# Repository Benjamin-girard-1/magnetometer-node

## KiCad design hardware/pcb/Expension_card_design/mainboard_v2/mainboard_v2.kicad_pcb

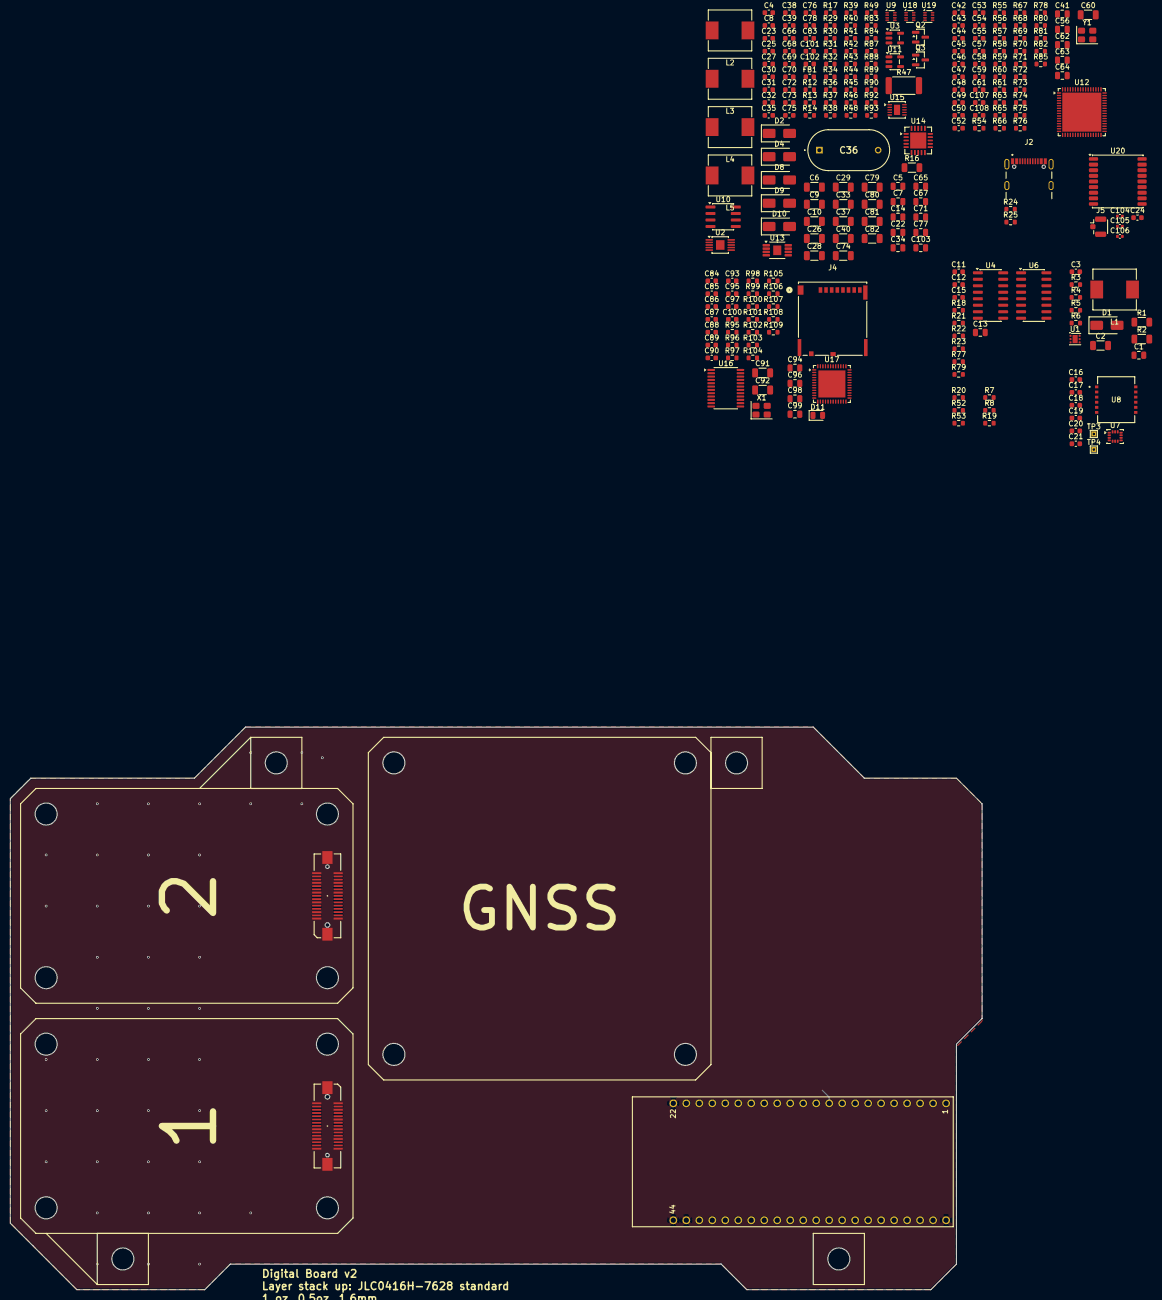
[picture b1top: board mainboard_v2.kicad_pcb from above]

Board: 4 copper layers, 190.0 x 110.0 mm, 260 parts (0 on the bottom side), 178 nets.

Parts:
C1, C7, C13, C22, C34, C41, C56, C65, C67, C71, C77, C96: 10u; C_0805_2012Metric
C2, C6, C9, C10, C37, C40, C79, C80, C81, C82, C91, C92: 4u7; C_1206_3216Metric
C3, C66, C68, C73, C78: 10n; C_0603_1608Metric
C4: 22p; C_0603_1608Metric
C5, C14, C62, C63, C64, C94, C98, C99, C103: 1u; C_0805_2012Metric
C8, C11, C12, C15, C16, C17, C18, C19, C20, C21, C23, C25, C38, C39, C42, C43, C44, C45, C46, C47, C48, C55, C58, C59, C61, C69, C72, C76, C84, C85, C86, C87, C88, C89, C90, C93, C95, C101, C102: 100n; C_0603_1608Metric
C24: 10u; C_0603_1608Metric
C26, C28: 22u; C_1206_3216Metric
C27, C97, C100: 15p; C_0603_1608Metric
C29, C33, C60, C74: 47u; C_1206_3216Metric
C30, C83: 4n7; C_0603_1608Metric
C31, C75: 10p; C_0603_1608Metric
C32, C35: 22n; C_0603_1608Metric
C36: 470mF; C_Radial_D8.0mm_P11.50mm
C49, C50, C52, C53, C54, C57, C107, C108: 1n; C_0603_1608Metric
C70: 220n; C_0603_1608Metric
C104, C105, C106: 100n; C_0402_1005Metric
D1, D2, D4, D8, D9, D10: SS34; D_SMA
D11: LED; LED_0805_2012Metric
FB1: 120Ω@100MHz 2A 50mΩ; L_0603_1608Metric
H1, H2, H3, H4, H5, H6, H7, H8, H9, H10, H11, H12, H13, H14, H15, H16: MountingHole; MountingHole_4.3mm_M4
J1, J3: 550910374; CONN_MOLEX_02x15_55091-0374
J2: USB_C_Receptacle_USB2.0_16P; GCT_USB4105-GF-A
J4: Micro_SD_CARD; CONN_503398-1892_MOL
J5: Conn_Coaxial; U.FL_Hirose_U.FL-R-SMT-1_Vertical
L1, L2, L3, L4, L5: 10u; ZEMS0850-100M_8.5x8.0mm
Q2: AO3401A; SOT-23
Q3: AO3400A; SOT-23
R1, R2: 0; R_1206_3216Metric
R3: 49k9; R_0603_1608Metric
R4, R7, R8, R17, R29, R31, R41, R42, R49, R52, R53, R56, R70, R73, R75, R78, R87, R90, R93, R95, R96, R108: 100k; R_0603_1608Metric
R5, R18, R19, R20, R39, R58, R77, R79, R97, R99, R100, R101, R102, R103, R104, R107, R109: 10k; R_0603_1608Metric
R6: 3k6; R_0603_1608Metric
R12, R92: 510k; R_0603_1608Metric
R13, R55, R80, R105: 1k; R_0603_1608Metric
R14, R48: 200k; R_0603_1608Metric
R16: 90k9; R_1206_3216Metric
R21, R22, R23, R57, R59, R60, R61, R63, R65, R66, R67, R68, R69, R71, R72, R74, R76, R81, R82, R85: 22; R_0603_1608Metric
R24, R25: 5k1; R_0603_1608Metric
R30, R32, R34, R37, R54: 300k; R_0603_1608Metric
R36: R_0603_1608Metric
R38, R43: 75k; R_0603_1608Metric
R40: 24k; R_0603_1608Metric
R44, R83: 39k; R_0603_1608Metric
R45, R46: 100; R_0603_1608Metric
R47: 22; R_2512_6332Metric
R84, R98: 12k; R_0603_1608Metric
R88: 330k; R_0603_1608Metric
R89: 10; R_0603_1608Metric
R106: 68k; R_0603_1608Metric
TP3, TP4: TestPoint; TestPoint_THTPad_1.0x1.0mm_Drill0.5mm
U1: TPS61170; WSON-6-1EP_2x2mm_P0.65mm_EP1x1.6mm
U2: LT3042xMSE; MSOP-10-1EP_3x3mm_P0.5mm_EP1.68x1.88mm
U3: TPS61040DBV; SOT-23-5
U4, U6: 74HC595D,118; SOIC-16_3.9x9.9mm_P1.27mm
U5: ESP32-S3-DevKitC; MODULE_ESP32-S3-DEVKITC
U7: LSM6DSVETR; LGA-14_3x2.5mm_P0.5mm_LayoutBorder3x4y
U8: SCL3300-D01-10; SCL3300-D01-10_MUR
U9, U18: TPS2116DRL; SOT-583-8
U10: TPS54331DR; SOIC-8_3.9x4.9mm_P1.27mm
U11: TPS7A2033PDBVR; SOT-23-5
U12: AD7779ACPZ; QFN-64-1EP_9x9mm_P0.5mm_EP7.65x7.65mm
U13: TPS7A4901DGNR; HVSSOP-8-1EP_3x3mm_P0.65mm_EP1.57x1.89mm
U14: TPS7A3301RGWR; Texas_RGW0020A_VQFN-20-1EP_5x5mm_P0.65mm_EP3.15x3.15mm
U15: TPS63700DRCR; VSON-10-1EP_3x3mm_P0.5mm_EP1.2x2mm
U16: TS3A27518EPWR; TSSOP-24_4.4x7.8mm_P0.65mm
U17: USB2641-HZH-02; QFN-48-1EP_7x7mm_P0.5mm_EP5.3x5.3mm
U19: TPS62933; SOT-583-8
U20: MAX-M10S; ublox_MAX
X1: X322524MOB4SI; Crystal_SMD_3225-4Pin_3.2x2.5mm
Y1: OT2JI-111-8.192M; Crystal_SMD_3225-4Pin_3.2x2.5mm

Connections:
+1V65: J1.17, J3.17, U12.57 (VCM)
+3V3: C11.1, C12.1, C13.1, C15.1, C16.2, C17.2, C18.2, C19.2, C24.1, C29.1, C47.1, C55.1, C56.1, C84.1, C85.1, C86.1, C87.1, C88.1, C89.1, C90.1, C91.1, C92.1, C93.1, C94.2, C95.1, C96.1, C104.1, C105.1, C106.1, J4.4 (VDD), L3.2, R18.1, R19.2, R20.2, R29.1, R38.1, R42.1, R58.2, R75.1, R77.1, R78.1, R79.1, R95.1, R96.1, R97.1, R99.1, R100.1, R101.1, R102.1, R103.1, R104.1, U4.16 (VCC), U5.1 (ESP_3V3), U5.2 (ESP_3V3), U6.16 (VCC), U7.5 (VDD_IO), U7.8 (VDD), U8.4 (VDD), U8.9 (DVIO), U12.24 (IOVDD), U16.8 (VCC), U17.5 (VDD33), U17.12 (VDD33), U17.16 (VDD33), U17.25 (VDD33), U17.34 (VDD33), U17.41 (VDD33), U17.48 (VDD33), U20.6 (V_BCKP), U20.7 (VCC_IO), U20.8 (VCC), Y1.4 (VDD)
+3V3A: C39.1, C40.1, C41.1, C42.1, C43.1, C44.1, C45.1, C46.1, J1.22, J3.22, U11.5 (OUT), U12.6 (AVDD1A), U12.43 (AVDD1B), U12.52 (AVDD2B), U12.54 (FORMAT1), U12.55 (FORMAT0), U12.58 (AVDD2A), U12.62 (AVDD4)
+3V3D: J1.23, J3.23
+5V: C10.1, C23.2, C37.1, C38.1, C77.1, C103.1, L2.1, Q2.2, R1.1, R30.2, R44.1, R89.2, U3.5 (VIN), U9.3 (VIN1), U9.5 (MODE), U11.1 (IN), U15.5 (IN), U18.2 (VOUT), U18.7 (VOUT)
+5VA: C66.1, C67.1, J1.19, J3.19, R83.1, U13.1 (OUT)
+9VA: C6.1, J1.21, J3.21, R54.1, U2.9 (OUTS), U2.10 (OUT)
+10V: C4.1, C5.1, C7.1, C8.1, C65.1, D2.1 (K), R12.1, U2.1 (IN), U2.2 (IN), U2.3 (EN/UV), U2.6 (PGFB), U13.5 (EN), U13.8 (IN)
+18V: J1.18, J3.18, R2.2
-5VA: C73.1, C74.1, J1.20, J3.20, R88.1, U14.1 (OUT), U14.20 (OUT)
-6V2: C71.1, C72.1, C78.1, C79.1, C80.1, C81.1, C82.1, D10.2 (A), R92.2, R93.2, U14.13 (EN), U14.15 (IN), U14.16 (IN), U15.8 (OUT)
/ADC_AD777x/ADC_9VA_MON: C48.1, R54.2, R55.1, R56.1
/ADC_AD777x/ADC_9VA_MON_FLT: R55.2, U12.63 (AUXAIN+)
/ADC_AD777x/ADC_AREG1CAP: C63.1, U12.59 (AREG1CAP)
/ADC_AD777x/ADC_AREG2CAP: C64.1, U12.51 (AREG2CAP)
/ADC_AD777x/ADC_CONVST_SAR: R70.1, U6.5 (QF), U12.17 (CONVST_SAR)
/ADC_AD777x/ADC_CS: R21.1, R58.1, U12.18 (ALERT/~CS)
/ADC_AD777x/ADC_DRDY: U5.16 (GPIO10), U12.30 (~DRDY)
/ADC_AD777x/ADC_DREGCAP: C62.1, U12.23 (DREGCAP)
/ADC_AD777x/ADC_IN0+: C49.1, R57.2, U12.2 (AIN0+)
/ADC_AD777x/ADC_IN0-: C49.2, R59.2, U12.1 (AIN0-)
/ADC_AD777x/ADC_IN1+: C50.1, R60.2, U12.4 (AIN1+)
/ADC_AD777x/ADC_IN1-: C50.2, R63.2, U12.3 (AIN1-)
/ADC_AD777x/ADC_IN2+: C52.1, R65.2, U12.10 (AIN2+)
/ADC_AD777x/ADC_IN2-: C52.2, R67.2, U12.9 (AIN2-)
/ADC_AD777x/ADC_IN3+: C57.1, C107.1, R66.2, R74.2, U12.12 (AIN3+), U12.37 (AIN7+)
/ADC_AD777x/ADC_IN3-: C57.2, C107.2, R76.2, R81.2, U12.11 (AIN3-), U12.38 (AIN7-)
/ADC_AD777x/ADC_IN4+: C53.1, R68.2, U12.47 (AIN4+)
/ADC_AD777x/ADC_IN4-: C53.2, R69.2, U12.48 (AIN4-)
/ADC_AD777x/ADC_IN5+: C54.1, R71.2, U12.45 (AIN5+)
/ADC_AD777x/ADC_IN5-: C54.2, R72.2, U12.46 (AIN5-)
/ADC_AD777x/ADC_IN6+: C108.1, R82.2, U12.39 (AIN6+)
/ADC_AD777x/ADC_IN6-: C108.2, R85.2, U12.40 (AIN6-)
/ADC_AD777x/ADC_MCLK: U12.32 (XTAL2/MCLK), Y1.3 (OUT)
/ADC_AD777x/ADC_MCLK_EN: R78.2, U6.4 (QE), Y1.1 (Tri-State)
/ADC_AD777x/ADC_REF+: C58.1, C59.1, C60.1, R80.1, U12.8 (REF1+), U12.41 (REF2+)
/ADC_AD777x/ADC_REF_OUT: C61.1, R80.2, U12.49 (REF_OUT)
/ADC_AD777x/ADC_RESET: R75.2, U6.2 (QC), U12.36 (~RESET)
/ADC_AD777x/ADC_SCLK: R22.1, U12.19 (DCLK2/SCLK)
/ADC_AD777x/ADC_SDI: R23.1, U12.20 (DCLK1/SDI)
/ADC_AD777x/ADC_SDO: R61.2, U5.20 (GPIO14)
/ADC_AD777x/ADC_SDO_R: R61.1, U12.21 (DCLK0/SDO)
/ADC_AD777x/ADC_START: R73.1, U6.3 (QD), U12.33 (~START)
/ADC_AD777x/AIN0+: J3.4, R59.1
/ADC_AD777x/AIN0-: J3.5, R57.1
/ADC_AD777x/AIN1+: J3.11, R63.1
/ADC_AD777x/AIN1-: J3.10, R60.1
/ADC_AD777x/AIN2+: J3.8, R65.1
/ADC_AD777x/AIN2-: J3.7, R67.1
/ADC_AD777x/AIN4+: J1.11, R69.1
/ADC_AD777x/AIN4-: J1.10, R68.1
/ADC_AD777x/AIN5+: J1.7, R71.1
/ADC_AD777x/AIN5-: J1.8, R72.1
/ADC_AD777x/AIN7+: J1.5, R74.1
/ADC_AD777x/AIN7-: J1.4, R76.1
/ADC_AD777x/TH1+: J3.13, R66.1
/ADC_AD777x/TH1-: J3.14, R81.1
/ADC_AD777x/TH2+: J1.13, R82.1
/ADC_AD777x/TH2-: J1.14, R85.1
/DATA_SAVING/+5VBUS: J2.A4 (VBUS), J2.B4 (VBUS), R106.1, R108.1
/DATA_SAVING/CC1: J2.B5 (CC2), R25.1
/DATA_SAVING/CC2: J2.A5 (CC1), R24.1
/DATA_SAVING/CRFLIT: C99.1, U17.15 (CRFILT)
/DATA_SAVING/D+: J2.A6 (D+), J2.B6 (D+), U17.42 (USB+)
/DATA_SAVING/D-: J2.A7 (D-), J2.B7 (D-), U17.43 (USB-)
/DATA_SAVING/EN_SD_MUX: R96.2, U4.6 (QG), U16.20 (~EN)
/DATA_SAVING/E_CLK: R101.2, U5.5 (GPIO5), U16.23 (NC3)
/DATA_SAVING/E_CMD: R102.2, U5.9 (GPIO16), U16.21 (NC4)
/DATA_SAVING/E_D0: R100.2, U5.6 (GPIO5), U16.1 (NC2)
/DATA_SAVING/E_D1: R99.2, U5.4 (GPIO4), U16.2 (NC1)
/DATA_SAVING/E_D2: R104.2, U5.7 (GPIO7), U16.22 (NC6)
/DATA_SAVING/E_D3: R103.2, U5.8 (GPIO15), U16.19 (NC5)
/DATA_SAVING/LED_IN: D11.2 (A), R105.2
/DATA_SAVING/LED_OUT: R105.1, U17.37 (LED)
/DATA_SAVING/MCLK: J4.5 (CLK), U16.7 (COM3)
/DATA_SAVING/MCMD: J4.3 (CMD), U16.9 (COM4)
/DATA_SAVING/MD0: J4.7 (DAT0), U16.6 (COM2)
/DATA_SAVING/MD1: J4.8 (DAT1), U16.4 (COM1)
/DATA_SAVING/MD2: J4.1 (DAT2), U16.12 (COM6)
/DATA_SAVING/MD3: J4.2 (DAT3), U16.10 (COM5)
/DATA_SAVING/PLL_FLIT: C98.1, U17.46 (PLLFILT)
/DATA_SAVING/RBIAS: R98.1, U17.47 (RBIAS)
/DATA_SAVING/SD_MUX_SEL: R95.2, U4.15 (QA), U16.14 (IN2), U16.24 (IN1)
/DATA_SAVING/SD_WP: R109.1, U17.13 (SD_WP)
/DATA_SAVING/SD_nCD: R107.1, U17.14 (SD_nCD)
/DATA_SAVING/USB2641_XTAL1: C100.1, U17.45 (XTAL1), X1.1
/DATA_SAVING/USB2641_XTAL2: C97.1, U17.44 (XTAL2), X1.3
/DATA_SAVING/USB2641_nRESET: R97.2, U4.5 (QF), U17.38 (nRESET)
/DATA_SAVING/USB_CLK: U16.15 (NO3), U17.21 (SD_CLK)
/DATA_SAVING/USB_CMD: U16.17 (NO4), U17.24 (SD_CMD)
/DATA_SAVING/USB_D0: U16.13 (NO2), U17.18 (SD_D0)
/DATA_SAVING/USB_D1: U16.11 (NO1), U17.17 (SD_D1)
/DATA_SAVING/USB_D2: U16.16 (NO6), U17.33 (SD_D2)
/DATA_SAVING/USB_D3: U16.18 (NO5), U17.32 (SD_D3)
/DATA_SAVING/VBUS_DET_3V: R106.2, U17.39 (VBUS_DET)
/DEVICE_DETECT_1: J3.2, R20.1, U5.13 (GPIO3)
/DEVICE_DETECT_2: J1.2, R19.1, U5.12 (GPIO8)
/GNSS/GPS_RX: U5.38 (GPIO48), U20.2 (TXD)
/GNSS/GPS_TX: U5.37 (GPIO45), U20.3 (RXD)
/IMU/CS_SCL: U5.14 (GPIO46), U8.5 (CS)
/IMU/MISO: U5.15 (GPIO9), U7.1 (SDO), U8.6 (MISO)
/IMU/MOSI: U5.11 (GPIO18), U7.14 (SDA), U8.7 (MOSI)
/IMU/SCLK: U5.10 (GPIO17), U7.13 (SCL), U8.8 (SCK)
/MCU_ESP32S3/EN_BST_18V: R4.1, U1.5 (CTRL), U4.3 (QD)
/MCU_ESP32S3/EN_SUPERCAP_CHARGE: R46.2, U5.28 (GPIO42)
/MCU_ESP32S3/ESP_CS: R21.2, U5.17 (GPIO11)
/MCU_ESP32S3/ESP_SCLK: R22.2, U5.18 (GPIO12)
/MCU_ESP32S3/ESP_SDO: R23.2, U5.19 (GPIO13)
/MCU_ESP32S3/SR_CHAIN_DATA: U4.9 (QH'), U6.14 (SER)
/MCU_ESP32S3/SR_DATA: U4.14 (SER), U5.42 (GPIO19)
/MCU_ESP32S3/SR_LATCH: U4.12 (RCLK), U5.40 (GPIO21), U6.12 (RCLK)
/MCU_ESP32S3/SR_OE_N: R18.2, U4.13 (~OE), U5.41 (GPIO20), U6.13 (~OE)
/MCU_ESP32S3/SR_SHIFT_CLK: U4.11 (SRCLK), U5.39 (GPIO47), U6.11 (SRCLK)
/POWER/5V_HOLDUP_CAP: C14.1, D9.1 (K), U9.6 (VIN2)
/POWER/5V_STEP_DOWN_IN: C28.1, R48.1, U9.2 (VOUT), U9.7 (VOUT), U10.2 (VIN)
/POWER/5V_SUPERCAP: C36.1, D9.2 (A), R47.2
/POWER/5V_USB_PRESENT: R29.2, U9.8 (ST)
/POWER/+5V_SOLAR: C27.2, C33.1, C102.2, L5.2, R32.2, R37.2, U18.3 (VIN1), U18.5 (MODE)
/POWER/BST_10V_FB: C4.2, R14.2, R17.1, U3.3 (FB)
/POWER/BST_10V_FB_DIV: R12.2, R14.1
/POWER/BST_10V_SW: D2.2 (A), L2.2, U3.1 (SW)
/POWER/INV_N5V5_COMP: C83.1, U15.1 (COMP)
/POWER/INV_N5V5_FB: C75.1, R87.2, R92.1, U15.9 (FB)
/POWER/INV_N5V5_FF: C75.2, R93.1
/POWER/INV_N5V5_SW: D10.1 (K), L4.1, U15.6 (SW)
/POWER/INV_N5V5_VIN: C69.1, R89.1, U15.3 (VIN)
/POWER/INV_N5V5_VREF: C70.1, R87.1, U15.10 (VREF)
/POWER/LDO_9V_ILIM: R13.2, U2.5 (ILIM)
/POWER/LDO_9V_SET: C9.1, R16.1, U2.7 (SET)
/POWER/LDO_N5V_FB: C73.2, R88.2, R90.1, U14.3 (FB)
/POWER/LDO_N5V_NR: C76.1, U14.14 (NR/SS)
/POWER/LDO_P5V_FB: C66.2, R83.2, R84.1, U13.2 (FB)
/POWER/LDO_P5V_NR: C68.1, U13.6 (NR/SS)
/POWER/SOLAR_PRESENT: R42.2, U18.8 (ST)
/POWER/SOLAR_VOLTAGE: C34.1, C101.2, R34.2, U19.3 (VIN)
/POWER/STPD_3V3_BOOT: C26.1, U10.1 (BOOT)
/POWER/STPD_3V3_COMP: C30.1, C31.1, U10.6 (COMP)
/POWER/STPD_3V3_COMP_F: C30.2, R39.1
/POWER/STPD_3V3_PH: C26.2, D4.1 (K), L3.1, U10.8 (PH)
/POWER/STPD_3V3_SS: C32.1, U10.4 (SS)
/POWER/STPD_3V3_VSENS: R38.2, R40.1, U10.5 (VSENSE)
/RESET_1: J3.26, R52.1, U6.6 (QG)
/RESET_2: J1.26, R7.1, U6.15 (QA)
/SCL_1: J3.28, U5.30 (GPIO40)
/SCL_2: J1.28, U5.27 (GPIO2)
/SDA_1: J3.29, U5.29 (GPIO41)
/SDA_2: J1.29, U5.26 (GPIO1)
/SENSOR_SET_RESET_DRIVER/+18V_OUT: C2.1, D1.1 (K), R2.1, R3.1
/SENSOR_SET_RESET_DRIVER/BST_18V_COMP: R5.1, U1.2 (COMP)
/SENSOR_SET_RESET_DRIVER/BST_18V_COMP_FILT: C3.1, R5.2
/SENSOR_SET_RESET_DRIVER/BST_18V_FB: R3.2, R6.1, U1.1 (FB)
/SENSOR_SET_RESET_DRIVER/BST_18V_IN: C1.1, L1.1, R1.2, U1.6 (VIN)
/SENSOR_SET_RESET_DRIVER/BST_18V_SW: D1.2 (A), L1.2, U1.4 (SW)
/SET_1: J3.25, R53.1, U6.7 (QH)
/SET_2: J1.25, R8.1, U6.1 (QB)
GND: C1.2, C2.2, C3.2, C5.2, C6.2, C7.2, C8.2, C9.2, C10.2, C11.2, C12.2, C13.2, C14.2, C15.2, C16.1, C17.1, C18.1, C19.1, C20.1, C21.1, C22.2, C23.1, C24.2, C28.2, C29.2, C31.2, C32.2, C33.2, C34.2, C35.2, C36.2, C37.2, C38.2, C39.2, C40.2, C41.2, C42.2, C43.2, C44.2, C45.2, C46.2, C47.2, C48.2, C55.2, C56.2, C58.2, C59.2, C60.2, C61.2, C62.2, C63.2, C64.2, C65.2, C67.2, C68.2, C69.2, C70.2, C71.2, C72.2, C74.2, C76.2, C77.2, C78.2, C79.2, C80.2, C81.2, C82.2, C83.2, C84.2, C85.2, C86.2, C87.2, C88.2, C89.2, C90.2, C91.2, C92.2, C93.2, C94.1, C95.2, C96.2, C97.2, C98.2, C99.2, C100.2, C101.1, C102.1, C103.2, C104.2, C105.2, C106.2, D4.2 (A), D11.1 (K), J1.1, J1.3, J1.6, J1.9, J1.12, J1.15, J1.16, J1.24, J1.27, J1.30, J1.P1, J1.P2, J2.A1 (GND), J2.B1 (GND), J2.S1 (SHIELD), J3.1, J3.3, J3.6, J3.9, J3.12, J3.15, J3.16, J3.24, J3.27, J3.30, J3.P1, J3.P2, J4.6 (VSS), J4.10 (SHIELD), J4.11 (VSS), J4.12 (VSS), J4.13 (VSS), J4.14 (VSS), J5.2 (Ext_2), L4.2, Q3.2, R4.2, R6.2, R7.2, R8.2, R13.1, R16.2, R17.2, R24.2, R25.2, R31.2, R36.2, R39.2, R40.2, R41.2, R43.2, R49.2, R52.2, R53.2, R56.2, R70.2, R73.2, R84.2, R90.2, R98.2, R107.2, R108.2, R109.2, U1.3 (GND), U1.7 (TP), U2.8 (GND), U2.11 (GND), U3.2 (GND), U4.8 (GND), U5.22 (GND), U5.23 (GND), U5.43 (GND), U5.44 (GND), U6.8 (GND), U7.2 (SDx), U7.3 (SCx), U7.6 (GND), U7.7 (GND), U8.1 (AVSS), U8.3 (RESERVED), U8.11 (DVSS), U8.12 (EMC_GND), U9.1 (GND), U10.7 (GND), U11.2 (GND), U11.4 (NC), U12.5 (AVSS1A), U12.7 (REF1-), U12.22 (DGND), U12.31 (XTAL1), U12.42 (REF2-), U12.44 (AVSS1B), U12.50 (AVSS2B), U12.53 (AVSS3), U12.56 (CLK_SEL), U12.60 (AVSS2A), U12.61 (AVSS4), U12.64 (AUXAIN-), U12.65 (EPAD(AVSSx)), U13.3 (NC), U13.4 (GND), U13.9 (PwPd), U14.7 (GND), U14.21 (EP), U15.2 (GND), U15.7 (PSGND), U15.11 (PowerPAD), U16.5 (GND), U17.40 (TEST), U17.49 (GND), U18.1 (GND), U19.4 (GND), U20.1 (GND), U20.10 (GND), U20.12 (GND), X1.2, X1.4, Y1.2 (GND)
unnamed: D8.2 (A), Q2.3
unnamed: D8.1 (K), R47.1
unnamed: Q2.1, R45.2
unnamed: Q3.1, R46.1, R49.1
unnamed: Q3.3, R44.2, R45.1
unnamed: R77.2, U4.10 (~SRCLR)
unnamed: R79.2, U6.10 (~SRCLR)
unnamed: TP3.1 (1_1), U7.4 (INT1)
unnamed: TP4.1 (1_1), U7.9 (INT2)
unnamed: C21.2, U8.2 (A_EXTC)
unnamed: C20.2, U8.10 (D_EXTC)
unnamed: R30.1, R31.1, U9.4 (PR1)
unnamed: R43.1, R48.2, U10.3 (EN)
unnamed: U12.34 (~SYNC_OUT), U12.35 (~SYNC_IN)
unnamed: R37.1, R41.1, U18.4 (PR1)
unnamed: C22.1, FB1.2, U18.6 (VIN2)
unnamed: C25.2, U19.6 (BST)
unnamed: R34.1, U19.2 (EN)
unnamed: C27.1, R32.1, U19.8 (FB)
unnamed: R36.1, U19.1 (RT)
unnamed: C35.1, U19.7 (SS)
unnamed: C25.1, L5.1, U19.5 (SW)

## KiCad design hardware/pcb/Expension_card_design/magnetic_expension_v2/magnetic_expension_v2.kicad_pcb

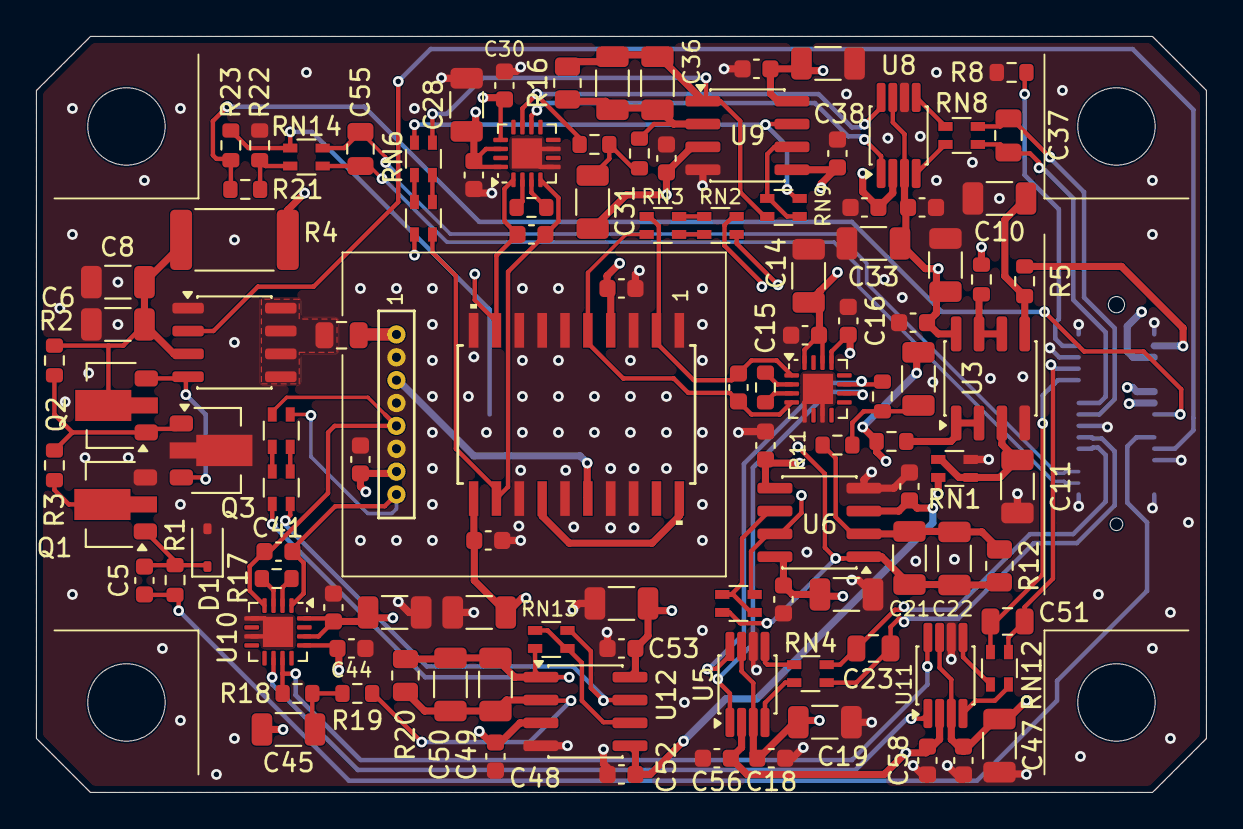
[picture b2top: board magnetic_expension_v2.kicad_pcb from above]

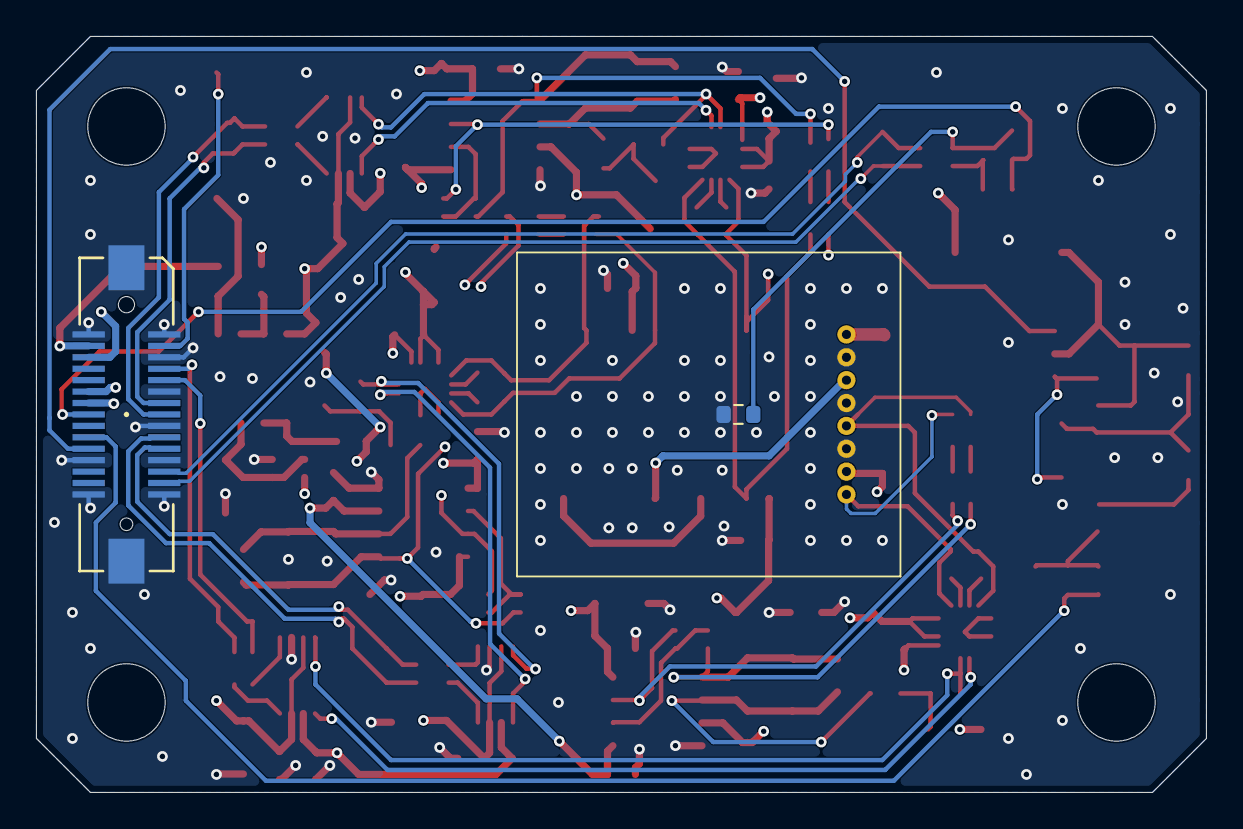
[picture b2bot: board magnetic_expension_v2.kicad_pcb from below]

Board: 4 copper layers, 65.0 x 42.0 mm, 118 parts (2 on the bottom side), 79 nets.

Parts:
C1, C6, C8: 10u; C_1206_3216Metric
C2, C3, C4, C9, C15, C16, C18, C20, C24, C25, C29, C30, C32, C34, C38, C39, C43, C44, C46, C48, C52, C53, C56, C57, C58: 100n; C_0603_1608Metric
C5: 1n; C_0603_1608Metric
C7, C23, C37, C51, C55: 220n; C_0805_2012Metric
C10, C11, C12, C14, C19, C21, C22, C26, C28, C33, C35, C36, C40, C42, C47, C49, C50, C54: 4u7; C_1206_3216Metric
C13, C27, C41: 10n; C_0603_1608Metric
C17, C31, C45: 47u; C_1206_3216Metric
D1: 1N4148WS; D_SOD-323
H1, H2, H3, H4: MountingHole; MountingHole_4.3mm_M4
J1: 528850374; CONN_MOLEX_02x15_52885-0374
Q1, Q2: D882; SOT-89-3
Q3: B772; SOT-89-3
Q4: DMC3028LSD; SO-8_3.9x4.9mm_P1.27mm
R1, R2, R3, R5: 1k; R_0603_1608Metric
R4: 220; R_2512_6332Metric
R6, R7: 20; R_0603_1608Metric
R8, R11, R15, R19: 20k; R_0603_1608Metric
R9, R13, R17: 120; R_0603_1608Metric
R10, R14, R18: 300k; R_0603_1608Metric
R12, R16, R20: 100M; R_0805_2012Metric
R21, R22, R23: 100k; R_0603_1608Metric
RN1: 10k; R_Array_Convex_2x0603
RN2, RN3, RN5, RN6, RN7, RN9, RN10, RN11, RN13: 20k; R_Array_Convex_2x0603
RN4, RN8, RN12, RN14: 1k; R_Array_Convex_2x0603
TH1: 100k NTC; R_0603_1608Metric
U1: HMC1001-RC; SIP8_HMC1001_HNW
U2: HMC1002-TR; SOIC20_HNW
U3, U6, U9, U12: OPA2197xD; SOIC-8_3.9x4.9mm_P1.27mm
U4, U7, U10: INA851RGTR; VQFN-16-1EP_3x3mm_P0.5mm_EP1.68x1.68mm
U5, U8, U11: THP210DGK; VSSOP-8_3x3mm_P0.65mm

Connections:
+1V65: J1.17, R5.1
+1V65B: C56.1, C57.1, C58.1, R7.2, U5.2 (VCM), U8.2 (VCM), U11.2 (VCM)
+3V3A: J1.23, R21.2, R23.2
+4V5B: C16.1, C17.2, C20.1, C24.1, C30.1, C31.2, C34.1, C38.1, C44.1, C45.2, C48.1, C52.1, R6.2, U4.13 (VOCM), U6.3 (+), U6.5 (+), U7.13 (VOCM), U9.3 (+), U9.5 (+), U10.13 (VOCM), U12.3 (+), U12.5 (+)
+9VA: C9.1, C12.1, C14.1, C15.1, C18.1, C19.1, C25.1, C26.1, C28.1, C29.1, C32.1, C33.1, C39.1, C40.1, C42.1, C43.1, C46.1, C47.1, C53.1, C54.1, J1.21, U3.8 (V+), U4.14 (VS+), U4.16 (VCLAMP+), U5.3 (V+), U5.7 (~PD), U6.8 (V+), U7.14 (VS+), U7.16 (VCLAMP+), U8.3 (V+), U8.7 (~PD), U9.8 (V+), U10.14 (VS+), U10.16 (VCLAMP+), U11.3 (V+), U11.7 (~PD), U12.8 (V+)
+9Vb: C1.1, C2.1, C3.1, C4.1, J1.22, RN1.2 (R2.1), U1.7 (VBRIDGE), U2.4 (VBRIDGE(A)), U2.11 (VBRIDGE(B))
+18V: J1.18, R4.2
/CONNECTOR/DEVICE_DETECT: J1.2, R8.1
/CONNECTOR/SENSOR_RESET_CTRL: J1.26, Q4.2 (G1)
/CONNECTOR/SENSOR_SET_CTRL: C5.1, J1.25, R1.1
/CONNECTOR/TH+: C55.1, J1.13, RN14.2 (R2.1)
/CONNECTOR/TH-: C55.2, J1.14, RN14.1 (R1.1)
/CONNECTOR/X_CONN+: C23.2, J1.10, RN4.1 (R1.1)
/CONNECTOR/X_CONN-: C23.1, J1.11, RN4.2 (R2.1)
/CONNECTOR/Y_CONN+: C37.2, J1.7, RN8.1 (R1.1)
/CONNECTOR/Y_CONN-: C37.1, J1.8, RN8.2 (R2.1)
/CONNECTOR/Z_CONN+: C51.2, J1.4, RN12.1 (R1.1)
/CONNECTOR/Z_CONN-: C51.1, J1.5, RN12.2 (R2.1)
/SENSOR_3AXIS_HMC100X/BR_X+: C13.1, RN3.1 (R1.1), U2.2 (OUT+(A)), U4.1 (IN-)
/SENSOR_3AXIS_HMC100X/BR_X-: C13.2, RN3.2 (R2.1), U2.5 (OUT-(A)), U4.4 (IN+)
/SENSOR_3AXIS_HMC100X/BR_Y+: C27.1, RN7.1 (R1.1), U2.9 (OUT+(B)), U7.1 (IN-)
/SENSOR_3AXIS_HMC100X/BR_Y-: C27.2, RN7.2 (R2.1), U2.12 (OUT-(B)), U7.4 (IN+)
/SENSOR_3AXIS_HMC100X/BR_Z+: C41.1, RN11.1 (R1.1), U1.8 (OUT-), U10.1 (IN-)
/SENSOR_3AXIS_HMC100X/BR_Z-: C41.2, RN11.2 (R2.1), U1.5 (OUT+), U10.4 (IN+)
/SENSOR_3AXIS_HMC100X/SETRESET_AFTER_1001: U1.3 (S/R-), U2.16 (S/R+(A))
/SENSOR_3AXIS_HMC100X/SETRESET_AFTER_1002A: U2.14 (S/R+(B)), U2.20 (S/R-(A))
/SENSOR_3AXIS_HMC100X/SETRESET_STRAP: C7.2, U1.1 (S/R+)
/SENSOR_SET_RESET_DRIVER/3V3_SET_CTRL: C5.2, D1.1 (K), Q1.1 (B), R1.2
/SENSOR_SET_RESET_DRIVER/18V_BUF: Q2.1 (B), Q3.1, R2.2, R3.1
/SENSOR_SET_RESET_DRIVER/18V_IN: C6.1, C8.1, Q2.2 (C), Q4.3 (S2), R2.1, R4.1
/SENSOR_SET_RESET_DRIVER/18V_PULSE: C7.1, Q4.5 (D2), Q4.6 (D2), Q4.7 (D1), Q4.8 (D1)
/SENSOR_SET_RESET_DRIVER/PULL_DOWN: Q1.2 (C), R3.2
/SENSOR_SET_RESET_DRIVER/PULSE_SET_CTRL: Q2.3 (E), Q3.3, Q4.4 (G2)
/THERMISTOR/TH_BRIDGE+: R21.1, R22.1, RN14.4 (R1.2)
/THERMISTOR/TH_BRIDGE-: R23.1, RN14.3 (R2.2), TH1.2
/VOLTAGE_REF/1V65_FB: R7.1, U3.6 (-), U3.7
/VOLTAGE_REF/1V65_FLTR: C10.1, R5.2, U3.5 (+)
/VOLTAGE_REF/4V5_DIV: C11.1, RN1.1 (R1.1), RN1.3 (R2.2), U3.3 (+)
/VOLTAGE_REF/4V5_FB: R6.1, U3.1, U3.2 (-)
/X_BALANCING/COMP+: C21.2, C22.2, R12.2, RN2.3 (R2.2), RN5.4 (R1.2), U6.1
/X_BALANCING/COMP-: RN2.4 (R1.2), RN5.2 (R2.1), U6.7
/X_BALANCING/INA_OUT+: R10.1, U4.11 (OUT+), U5.8 (+)
/X_BALANCING/INA_OUT-: U4.10 (OUT-), U5.1 (-)
/X_BALANCING/INA_OUT_FLTR+: C17.1, R10.2, R11.1
/X_BALANCING/INT_FB: C21.1, C22.1, R11.2, R12.1, U6.2 (-)
/X_BALANCING/INV_FB: RN5.1 (R1.1), RN5.3 (R2.2), U6.6 (-)
/X_BALANCING/THP_OUT+: RN4.4 (R1.2), U5.4
/X_BALANCING/THP_OUT-: RN4.3 (R2.2), U5.5
/X_BALANCING/X_RG+: R9.2, U4.2 (RG+)
/X_BALANCING/X_RG-: R9.1, U4.3 (RG-)
/Y_BALANCING/COMP+: C35.2, C36.2, R16.2, RN6.3 (R2.2), RN9.4 (R1.2), U9.1
/Y_BALANCING/COMP-: RN6.4 (R1.2), RN9.2 (R2.1), U9.7
/Y_BALANCING/INA_OUT+: R14.1, U7.11 (OUT+), U8.8 (+)
/Y_BALANCING/INA_OUT-: U7.10 (OUT-), U8.1 (-)
/Y_BALANCING/INA_OUT_FLTR+: C31.1, R14.2, R15.1
/Y_BALANCING/INT_FB: C35.1, C36.1, R15.2, R16.1, U9.2 (-)
/Y_BALANCING/INV_FB: RN9.1 (R1.1), RN9.3 (R2.2), U9.6 (-)
/Y_BALANCING/THP_OUT+: RN8.4 (R1.2), U8.4
/Y_BALANCING/THP_OUT-: RN8.3 (R2.2), U8.5
/Y_BALANCING/X_RG+: R13.2, U7.2 (RG+)
/Y_BALANCING/X_RG-: R13.1, U7.3 (RG-)
/Z_BALANCING/COMP+: C49.2, C50.2, R20.2, RN10.3 (R2.2), RN13.4 (R1.2), U12.1
/Z_BALANCING/COMP-: RN10.4 (R1.2), RN13.2 (R2.1), U12.7
/Z_BALANCING/INA_OUT+: R18.1, U10.11 (OUT+), U11.8 (+)
/Z_BALANCING/INA_OUT-: U10.10 (OUT-), U11.1 (-)
/Z_BALANCING/INA_OUT_FLTR+: C45.1, R18.2, R19.1
/Z_BALANCING/INT_FB: C49.1, C50.1, R19.2, R20.1, U12.2 (-)
/Z_BALANCING/INV_FB: RN13.1 (R1.1), RN13.3 (R2.2), U12.6 (-)
/Z_BALANCING/THP_OUT+: RN12.4 (R1.2), U11.4
/Z_BALANCING/THP_OUT-: RN12.3 (R2.2), U11.5
/Z_BALANCING/X_RG+: R17.2, U10.2 (RG+)
/Z_BALANCING/X_RG-: R17.1, U10.3 (RG-)
GND: C1.2, C2.2, C3.2, C4.2, C6.2, C8.2, C9.2, C10.2, C11.2, C12.2, C14.2, C15.2, C16.2, C18.2, C19.2, C20.2, C24.2, C25.2, C26.2, C28.2, C29.2, C30.2, C32.2, C33.2, C34.2, C38.2, C39.2, C40.2, C42.2, C43.2, C44.2, C46.2, C47.2, C48.2, C52.2, C53.2, C54.2, C56.2, C57.2, C58.2, D1.2 (A), J1.1, J1.3, J1.6, J1.9, J1.12, J1.15, J1.16, J1.27, J1.30, J1.P1, J1.P2, Q1.3 (E), Q3.2, Q4.1 (S1), R8.2, R22.2, RN1.4 (R1.2), TH1.1, U1.2 (OFFSET+), U1.4 (GND), U1.6 (OFFSET-), U2.1 (GND1(A)), U2.3 (OFFSET-(A)), U2.6 (GND2(A)), U2.7 (S/R-(B)), U2.8 (GND1(B)), U2.10 (OFFSET-(B)), U2.13 (GND2(B)), U2.15 (OFFSET+(B)), U2.17 (OFFSET(+A)), U2.18 (GND_PLN), U3.4 (V-), U4.5 (VCLAMP-), U4.7 (VS-), U4.17 (TP), U5.6 (V-), U6.4 (V-), U7.5 (VCLAMP-), U7.7 (VS-), U7.17 (TP), U8.6 (V-), U9.4 (V-), U10.5 (VCLAMP-), U10.7 (VS-), U10.17 (TP), U11.6 (V-), U12.4 (V-)
unnamed: RN2.1 (R1.1), RN3.4 (R1.2)
unnamed: RN2.2 (R2.1), RN3.3 (R2.2)
unnamed: RN6.1 (R1.1), RN7.4 (R1.2)
unnamed: RN6.2 (R2.1), RN7.3 (R2.2)
unnamed: RN10.1 (R1.1), RN11.4 (R1.2)
unnamed: RN10.2 (R2.1), RN11.3 (R2.2)

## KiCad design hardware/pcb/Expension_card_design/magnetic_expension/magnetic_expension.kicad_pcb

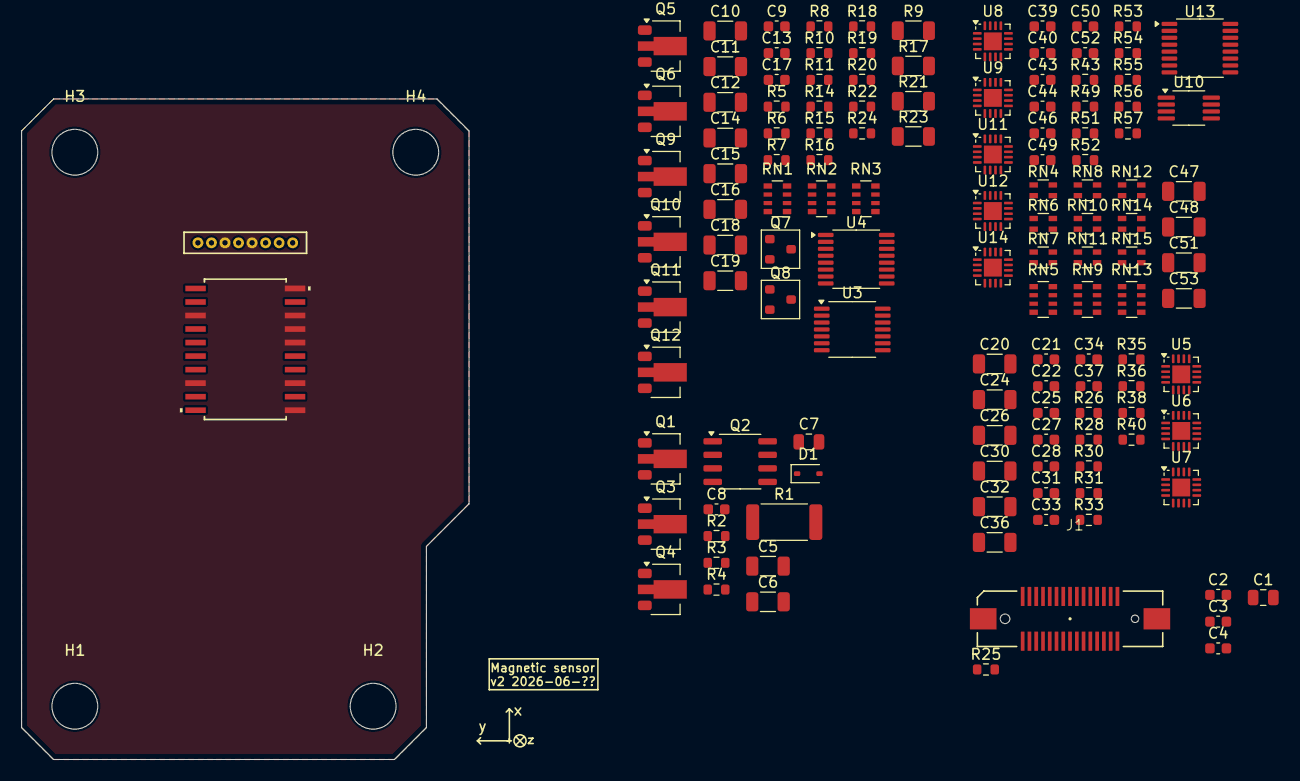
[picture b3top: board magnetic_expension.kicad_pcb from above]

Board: 4 copper layers, 42.0 x 62.0 mm, 134 parts (0 on the bottom side), 101 nets, no tracks yet.

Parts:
C1: 10u; C_0805_2012Metric
C2, C3, C4, C9, C13, C17, C21, C25, C27, C31, C33, C37, C46, C52: 100n; C_0603_1608Metric
C5, C6: 10u; C_1206_3216Metric
C7: 220n; C_0805_2012Metric
C8, C39, C43, C49: 1n; C_0603_1608Metric
C10, C11, C12, C14, C15, C16, C18, C19, C20, C24, C26, C30, C32, C36, C47, C48, C51, C53: 4u7; C_1206_3216Metric
C22, C28, C34: 10n; C_0603_1608Metric
C40, C44, C50: 220n; C_0603_1608Metric
D1: 1N4148WS; D_SOD-323
H1, H2, H3, H4: MountingHole; MountingHole_4.3mm_M4
J1: 528850374; CONN_MOLEX_02x15_52885-0374
Q1, Q4, Q5, Q9, Q11: D882; SOT-89-3
Q2: DMC3028LSD; SO-8_3.9x4.9mm_P1.27mm
Q3, Q6, Q10, Q12: B772; SOT-89-3
Q7: MMBT5551; SOT-23
Q8: MMBT5401; SOT-23
R1: 220; R_2512_6332Metric
R2, R3, R4, R43, R49, R51, R52, R53, R55, R56, R57: 1k; R_0603_1608Metric
R5, R10, R14, R18, R19, R24: 470; R_0603_1608Metric
R6, R8, R15, R16, R20, R22: 22k; R_0603_1608Metric
R7: 10; R_0603_1608Metric
R9, R17, R23: 200; R_1206_3216Metric
R11, R25, R54: 20k; R_0603_1608Metric
R21: 20; R_1206_3216Metric
R26, R30, R31, R35, R36, R40: 49.9; R_0603_1608Metric
R28, R33, R38: 100; R_0603_1608Metric
RN1, RN2, RN3, RN5, RN9, RN13: 10k; R_Array_Convex_4x0603
RN4, RN8, RN12: 20k; R_Array_Convex_2x0603
RN6, RN7, RN10, RN11, RN14, RN15: 5k; R_Array_Convex_2x0603
U1: HMC1001-RC; SIP8_HMC1001_HNW
U2: HMC1002-TR; SOIC20_HNW
U3: OPA4197xPW; TSSOP-14_4.4x5mm_P0.65mm
U4, U13: DAC7678SPWR; TSSOP-16_4.4x5mm_P0.65mm
U5, U6, U7: INA851RGTR; VQFN-16-1EP_3x3mm_P0.5mm_EP1.68x1.68mm
U8, U9, U11, U12, U14: THS4551IRGTR; VQFN-16-1EP_3x3mm_P0.5mm_EP1.68x1.68mm
U10: DAC8571IDGK; MSOP-8_3x3mm_P0.65mm

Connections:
+1V65: J1.17, U3.12 (+)
+1V65B: C17.1, R21.2, U5.13 (VOCM), U6.13 (VOCM), U7.13 (VOCM), U8.9 (V_{OCM}), U9.9 (V_{OCM}), U11.9 (V_{OCM}), U12.9 (V_{OCM}), U14.9 (V_{OCM})
+3V3A: C46.1, C47.1, C52.1, C53.1, J1.22, U5.16 (VCLAMP+), U6.16 (VCLAMP+), U7.16 (VCLAMP+), U8.5 (V_{S+}), U8.6 (V_{S+}), U8.7 (V_{S+}), U8.8 (V_{S+}), U9.5 (V_{S+}), U9.6 (V_{S+}), U9.7 (V_{S+}), U9.8 (V_{S+}), U11.5 (V_{S+}), U11.6 (V_{S+}), U11.7 (V_{S+}), U11.8 (V_{S+}), U11.12 (~PD), U12.5 (V_{S+}), U12.6 (V_{S+}), U12.7 (V_{S+}), U12.8 (V_{S+}), U12.12 (~PD), U13.2 (ADDR0), U13.3 (AV_{DD}), U13.8 (V_{REFIN}/V_{REFOUT}), U14.5 (V_{S+}), U14.6 (V_{S+}), U14.7 (V_{S+}), U14.8 (V_{S+}), U14.12 (~PD)
+5VA: C20.1, C21.1, C24.1, C25.1, C30.1, C31.1, J1.19, Q5.2, Q9.2, Q11.2, R7.1, R11.2, R54.2, U3.4 (V+), U5.14 (VS+), U6.14 (VS+), U7.14 (VS+)
+9VA: C1.1, C2.1, C3.1, C4.1, J1.21, U1.7 (VBRIDGE), U2.4 (VBRIDGE(A)), U2.11 (VBRIDGE(B))
+18V: J1.18, R1.2
-5VA: C26.1, C27.1, C32.1, C33.1, C36.1, C37.1, J1.20, Q6.2, Q10.2, Q12.2, U3.11 (V-), U5.7 (VS-), U6.7 (VS-), U7.7 (VS-)
/BRIDGE_OFFSET/DAC_B_OUTA: RN5.8 (R1.2), U13.4 (V_{OUT}A)
/BRIDGE_OFFSET/DAC_B_OUTB: RN5.6 (R3.2), U13.13 (V_{OUT}B)
/BRIDGE_OFFSET/DAC_B_OUTC: RN9.8 (R1.2), U13.5 (V_{OUT}C)
/BRIDGE_OFFSET/DAC_B_OUTD: RN9.6 (R3.2), U13.12 (V_{OUT}D)
/BRIDGE_OFFSET/DAC_B_OUTE: RN13.8 (R1.2), U13.6 (V_{OUT}E)
/BRIDGE_OFFSET/DAC_B_OUTF: RN13.6 (R3.2), U13.11 (V_{OUT}F)
/BRIDGE_OFFSET/V_{OUT}+: R49.2, U9.10 (+)
/BRIDGE_OFFSET/V_{OUT}-: R43.2, U9.11 (-)
/BRIDGE_OFFSET/X_COMP_FILT+: RN5.1 (R1.1), RN5.7 (R2.2)
/BRIDGE_OFFSET/X_COMP_FILT-: RN5.3 (R3.1), RN5.5 (R4.2)
/BRIDGE_OFFSET/X_CONN+: C40.2, C50.2, J1.10, R52.2, R57.2
/BRIDGE_OFFSET/X_CONN-: C40.1, C50.1, J1.11, R51.2, R56.2
/BRIDGE_OFFSET/X_INA_FILT+: C39.1, RN6.2 (R2.1), RN7.3 (R2.2)
/BRIDGE_OFFSET/X_INA_FILT-: C39.2, RN6.1 (R1.1), RN7.4 (R1.2)
/BRIDGE_OFFSET/X_SUM_FB+: RN4.3 (R2.2), RN5.4 (R4.1), RN7.2 (R2.1), U11.3 (-)
/BRIDGE_OFFSET/X_SUM_FB-: RN4.4 (R1.2), RN5.2 (R2.1), RN7.1 (R1.1), U11.2 (+)
/BRIDGE_OFFSET/X_SUM_OUT+: R52.1, RN4.2 (R2.1), U11.10 (+)
/BRIDGE_OFFSET/X_SUM_OUT-: R51.1, RN4.1 (R1.1), U11.11 (-)
/BRIDGE_OFFSET/Y_COMP_FILT+: RN9.1 (R1.1), RN9.7 (R2.2)
/BRIDGE_OFFSET/Y_COMP_FILT-: RN9.3 (R3.1), RN9.5 (R4.2)
/BRIDGE_OFFSET/Y_CONN+: C44.2, J1.7, R55.2
/BRIDGE_OFFSET/Y_CONN-: C44.1, J1.8, R53.2
/BRIDGE_OFFSET/Y_INA_FILT+: C43.1, RN10.2 (R2.1), RN11.3 (R2.2)
/BRIDGE_OFFSET/Y_INA_FILT-: C43.2, RN10.1 (R1.1), RN11.4 (R1.2)
/BRIDGE_OFFSET/Y_SUM_FB+: RN8.3 (R2.2), RN9.4 (R4.1), RN11.2 (R2.1), U12.3 (-)
/BRIDGE_OFFSET/Y_SUM_FB-: RN8.4 (R1.2), RN9.2 (R2.1), RN11.1 (R1.1), U12.2 (+)
/BRIDGE_OFFSET/Y_SUM_OUT+: R55.1, RN8.2 (R2.1), U12.10 (+)
/BRIDGE_OFFSET/Y_SUM_OUT-: R53.1, RN8.1 (R1.1), U12.11 (-)
/BRIDGE_OFFSET/Z_COMP_FILT+: C48.1, RN13.1 (R1.1), RN13.7 (R2.2)
/BRIDGE_OFFSET/Z_COMP_FILT-: C51.1, RN13.3 (R3.1), RN13.5 (R4.2)
/BRIDGE_OFFSET/Z_INA_FILT+: C49.1, RN14.2 (R2.1), RN15.3 (R2.2)
/BRIDGE_OFFSET/Z_INA_FILT-: C49.2, RN14.1 (R1.1), RN15.4 (R1.2)
/BRIDGE_OFFSET/Z_SUM_FB+: RN12.3 (R2.2), RN13.4 (R4.1), RN15.2 (R2.1), U14.3 (-)
/BRIDGE_OFFSET/Z_SUM_FB-: RN12.4 (R1.2), RN13.2 (R2.1), RN15.1 (R1.1), U14.2 (+)
/BRIDGE_OFFSET/Z_SUM_OUT+: R57.1, RN12.2 (R2.1), U14.10 (+)
/BRIDGE_OFFSET/Z_SUM_OUT-: R56.1, RN12.1 (R1.1), U14.11 (-)
/CONNECTOR/DEVICE_DETECT: J1.2, R25.1
/CONNECTOR/I2C.SCL: J1.28, U4.16 (SCL)
/CONNECTOR/I2C.SDA: J1.29, U4.15 (SDA)
/CONNECTOR/SENSOR_RESET_CTRL: J1.26, Q2.2 (G1)
/CONNECTOR/SENSOR_SET_CTRL: C8.1, J1.25, R4.1
/INA_GAIN/BR_FTL_X+: C22.1, C28.1, C34.1, R26.2, R31.2, R36.2, U5.1 (IN-), U6.1 (IN-), U7.1 (IN-)
/INA_GAIN/BR_FTL_X-: C22.2, C28.2, C34.2, R30.2, R35.2, R40.2, U5.4 (IN+), U6.4 (IN+), U7.4 (IN+)
/INA_GAIN/BR_X+: R26.1, U2.2 (OUT+(A))
/INA_GAIN/BR_X-: R30.1, U2.5 (OUT-(A))
/INA_GAIN/BR_Y+: R36.1, U2.9 (OUT+(B))
/INA_GAIN/BR_Y-: R40.1, U2.12 (OUT-(B))
/INA_GAIN/BR_Z+: R31.1, U1.8 (OUT-)
/INA_GAIN/BR_Z-: R35.1, U1.5 (OUT+)
/INA_GAIN/X_RG+: R28.2, U5.2 (RG+)
/INA_GAIN/X_RG-: R28.1, U5.3 (RG-)
/INA_GAIN/Y_RG+: R38.2, U7.2 (RG+)
/INA_GAIN/Y_RG-: R38.1, U7.3 (RG-)
/INA_GAIN/Z_RG+: R33.2, U6.2 (RG+)
/INA_GAIN/Z_RG-: R33.1, U6.3 (RG-)
/MAGNETIC_OFFSET_DRIVERS/1V65_FB: R21.1, U3.13 (-), U3.14
/MAGNETIC_OFFSET_DRIVERS/OFFSET_X+: R9.2, RN1.5, U2.17 (OFFSET(+A))
/MAGNETIC_OFFSET_DRIVERS/OFFSET_Y+: R17.2, RN2.5, U2.15 (OFFSET+(B))
/MAGNETIC_OFFSET_DRIVERS/OFFSET_Z+: R23.2, RN3.5, U1.2 (OFFSET+)
/MAGNETIC_OFFSET_DRIVERS/OFF_X_BN: Q5.1, R5.2, R6.2
/MAGNETIC_OFFSET_DRIVERS/OFF_X_BP: Q6.1, R8.2, R10.2
/MAGNETIC_OFFSET_DRIVERS/OFF_X_DRV: R5.1, R10.1, U3.1
/MAGNETIC_OFFSET_DRIVERS/OFF_X_INN: C11.1, RN1.4, RN1.7, U3.2 (-)
/MAGNETIC_OFFSET_DRIVERS/OFF_X_INP: C12.1, RN1.3, RN1.8, U3.3 (+)
/MAGNETIC_OFFSET_DRIVERS/OFF_X_SENSE_P: Q5.3, Q6.3, R6.1, R8.1, R9.1, RN1.6
/MAGNETIC_OFFSET_DRIVERS/OFF_Y_BN: Q9.1, R14.2, R15.2
/MAGNETIC_OFFSET_DRIVERS/OFF_Y_BP: Q10.1, R16.2, R18.2
/MAGNETIC_OFFSET_DRIVERS/OFF_Y_DRV: R14.1, R18.1, U3.7
/MAGNETIC_OFFSET_DRIVERS/OFF_Y_INN: C15.1, RN2.4, RN2.7, U3.6 (-)
/MAGNETIC_OFFSET_DRIVERS/OFF_Y_INP: C16.1, RN2.3, RN2.8, U3.5 (+)
/MAGNETIC_OFFSET_DRIVERS/OFF_Y_SENSE_P: Q9.3, Q10.3, R15.1, R16.1, R17.1, RN2.6
/MAGNETIC_OFFSET_DRIVERS/OFF_Z_BN: Q11.1, R19.2, R20.2
/MAGNETIC_OFFSET_DRIVERS/OFF_Z_BP: Q12.1, R22.2, R24.2
/MAGNETIC_OFFSET_DRIVERS/OFF_Z_DRV: R19.1, R24.1, U3.8
/MAGNETIC_OFFSET_DRIVERS/OFF_Z_INN: C18.1, RN3.4, RN3.7, U3.9 (-)
/MAGNETIC_OFFSET_DRIVERS/OFF_Z_INP: C19.1, RN3.3, RN3.8, U3.10 (+)
/MAGNETIC_OFFSET_DRIVERS/OFF_Z_SENSE_P: Q11.3, Q12.3, R20.1, R22.1, R23.1, RN3.6
/SENSOR_3AXIS_HMC100X/SETRESET_AFTER_1001: U1.3 (S/R-), U2.16 (S/R+(A))
/SENSOR_3AXIS_HMC100X/SETRESET_AFTER_1002A: U2.14 (S/R+(B)), U2.20 (S/R-(A))
/SENSOR_3AXIS_HMC100X/SETRESET_STRAP: C7.2, U1.1 (S/R+)
/SENSOR_SET_RESET_DRIVER/3V3_SET_CTRL: C8.2, D1.1 (K), Q4.1 (B), R4.2
/SENSOR_SET_RESET_DRIVER/18V_BUF: Q1.1 (B), Q3.1, R2.2, R3.1
/SENSOR_SET_RESET_DRIVER/18V_IN: C5.1, C6.1, Q1.2 (C), Q2.3 (S2), R1.1, R2.1
/SENSOR_SET_RESET_DRIVER/18V_PULSE: C7.1, Q2.5 (D2), Q2.6 (D2), Q2.7 (D1), Q2.8 (D1)
/SENSOR_SET_RESET_DRIVER/PULL_DOWN: Q4.2 (C), R3.2
/SENSOR_SET_RESET_DRIVER/PULSE_SET_CTRL: Q1.3 (E), Q2.4 (G2), Q3.3
GND: C1.2, C2.2, C3.2, C4.2, C5.2, C6.2, C9.2, C10.2, C11.2, C12.2, C13.2, C14.2, C15.2, C16.2, C17.2, C18.2, C19.2, C20.2, C21.2, C24.2, C25.2, C26.2, C27.2, C30.2, C31.2, C32.2, C33.2, C36.2, C37.2, C46.2, C47.2, C48.2, C51.2, C52.2, C53.2, D1.2 (A), J1.1, J1.3, J1.6, J1.9, J1.12, J1.15, J1.16, J1.24, J1.27, J1.30, J1.P1, J1.P2, Q2.1 (S1), Q3.2, Q4.3 (E), R25.2, U1.4 (GND), U1.6 (OFFSET-), U2.1 (GND1(A)), U2.3 (OFFSET-(A)), U2.6 (GND2(A)), U2.7 (S/R-(B)), U2.8 (GND1(B)), U2.10 (OFFSET-(B)), U2.13 (GND2(B)), U2.18 (GND_PLN), U4.2 (ADDR0), U4.14 (GND), U5.5 (VCLAMP-), U5.17 (TP), U6.5 (VCLAMP-), U6.17 (TP), U7.5 (VCLAMP-), U7.17 (TP), U8.13 (V_{S-}), U8.14 (V_{S-}), U8.15 (V_{S-}), U8.16 (V_{S-}), U8.17 (EP), U9.13 (V_{S-}), U9.14 (V_{S-}), U9.15 (V_{S-}), U9.16 (V_{S-}), U9.17 (EP), U10.8 (GND), U11.13 (V_{S-}), U11.14 (V_{S-}), U11.15 (V_{S-}), U11.16 (V_{S-}), U11.17 (EP), U12.13 (V_{S-}), U12.14 (V_{S-}), U12.15 (V_{S-}), U12.16 (V_{S-}), U12.17 (EP), U13.14 (GND), U14.13 (V_{S-}), U14.14 (V_{S-}), U14.15 (V_{S-}), U14.16 (V_{S-}), U14.17 (EP)
unnamed: Q7.2 (E), Q8.2 (E)
unnamed: R43.1, U9.2 (+)
unnamed: R49.1, U9.3 (-)
unnamed: C9.1, C10.1, R7.2, U4.3 (AV_{DD})
unnamed: C13.1, C14.1, U4.8 (V_{REFIN}/V_{REFOUT})
unnamed: R11.1, U4.9 (~CLR)
unnamed: R54.1, U13.9 (~CLR)
